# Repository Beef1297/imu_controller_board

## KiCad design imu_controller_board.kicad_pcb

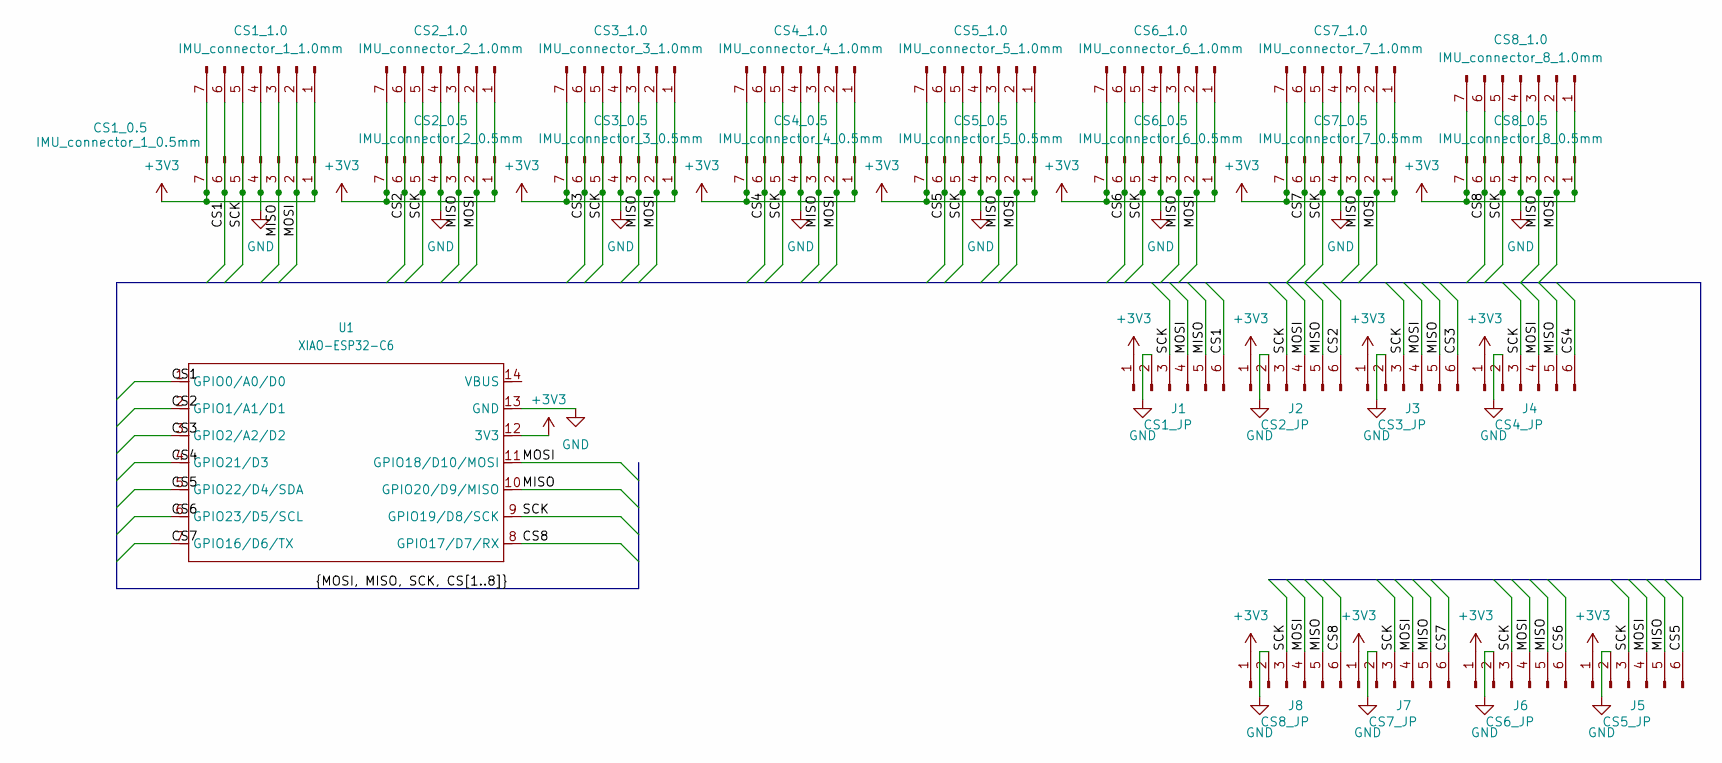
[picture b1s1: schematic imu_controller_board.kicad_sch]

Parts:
CS1_0.5: IMU_connector_1_0.5mm; FC-5A7P11H20-05pitch_7pin
CS1_1.0: IMU_connector_1_1.0mm; FPC-SMD_XUNPU_FPC-1.0FX-7PWCR-H20
CS2_0.5: IMU_connector_2_0.5mm; FC-5A7P11H20-05pitch_7pin
CS2_1.0: IMU_connector_2_1.0mm; FPC-SMD_XUNPU_FPC-1.0FX-7PWCR-H20
CS3_0.5: IMU_connector_3_0.5mm; FC-5A7P11H20-05pitch_7pin
CS3_1.0: IMU_connector_3_1.0mm; FPC-SMD_XUNPU_FPC-1.0FX-7PWCR-H20
CS4_0.5: IMU_connector_4_0.5mm; FC-5A7P11H20-05pitch_7pin
CS4_1.0: IMU_connector_4_1.0mm; FPC-SMD_XUNPU_FPC-1.0FX-7PWCR-H20
CS5_0.5: IMU_connector_5_0.5mm; FC-5A7P11H20-05pitch_7pin
CS5_1.0: IMU_connector_5_1.0mm; FPC-SMD_XUNPU_FPC-1.0FX-7PWCR-H20
CS6_0.5: IMU_connector_6_0.5mm; FC-5A7P11H20-05pitch_7pin
CS6_1.0: IMU_connector_6_1.0mm; FPC-SMD_XUNPU_FPC-1.0FX-7PWCR-H20
CS7_0.5: IMU_connector_7_0.5mm; FC-5A7P11H20-05pitch_7pin
CS7_1.0: IMU_connector_7_1.0mm; FPC-SMD_XUNPU_FPC-1.0FX-7PWCR-H20
CS8_0.5: IMU_connector_8_0.5mm; FC-5A7P11H20-05pitch_7pin
CS8_1.0: IMU_connector_8_1.0mm; FPC-SMD_XUNPU_FPC-1.0FX-7PWCR-H20
J1: CS1_JP; PinHeader_1x06_P2.54mm_Vertical
J2: CS2_JP; PinHeader_1x06_P2.54mm_Vertical
J3: CS3_JP; PinHeader_1x06_P2.54mm_Vertical
J4: CS4_JP; PinHeader_1x06_P2.54mm_Vertical
J5: CS5_JP; PinHeader_1x06_P2.54mm_Vertical
J6: CS6_JP; PinHeader_1x06_P2.54mm_Vertical
J7: CS7_JP; PinHeader_1x06_P2.54mm_Vertical
J8: CS8_JP; PinHeader_1x06_P2.54mm_Vertical
U1: XIAO-ESP32-C6; XIAO-ESP32C6-DIP

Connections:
+3V3: CS1_0.5.1, CS1_0.5.7, CS1_1.0.1, CS1_1.0.7, CS2_0.5.1, CS2_0.5.7, CS2_1.0.1, CS2_1.0.7, CS3_0.5.1, CS3_0.5.7, CS3_1.0.1, CS3_1.0.7, CS4_0.5.1, CS4_0.5.7, CS4_1.0.1, CS4_1.0.7, CS5_0.5.1, CS5_0.5.7, CS5_1.0.1, CS5_1.0.7, CS6_0.5.1, CS6_0.5.7, CS6_1.0.1, CS6_1.0.7, CS7_0.5.1, CS7_0.5.7, CS7_1.0.1, CS7_1.0.7, CS8_0.5.1, CS8_0.5.7, CS8_1.0.1, CS8_1.0.7, J1.1, J2.1, J3.1, J4.1, J5.1, J6.1, J7.1, J8.1, U1.12 (3V3)
/CS1: CS1_0.5.6, CS1_1.0.6, J1.6, U1.1 (GPIO0/A0/D0)
/CS2: CS2_0.5.6, CS2_1.0.6, J2.6, U1.2 (GPIO1/A1/D1)
/CS3: CS3_0.5.6, CS3_1.0.6, J3.6, U1.3 (GPIO2/A2/D2)
/CS4: CS4_0.5.6, CS4_1.0.6, J4.6, U1.4 (GPIO21/D3)
/CS5: CS5_0.5.6, CS5_1.0.6, J5.6, U1.5 (GPIO22/D4/SDA)
/CS6: CS6_0.5.6, CS6_1.0.6, J6.6, U1.6 (GPIO23/D5/SCL)
/CS7: CS7_0.5.6, CS7_1.0.6, J7.6, U1.7 (GPIO16/D6/TX)
/CS8: CS8_0.5.6, CS8_1.0.6, J8.6, U1.8 (GPIO17/D7/RX)
/MISO: CS1_0.5.3, CS1_1.0.3, CS2_0.5.3, CS2_1.0.3, CS3_0.5.3, CS3_1.0.3, CS4_0.5.3, CS4_1.0.3, CS5_0.5.3, CS5_1.0.3, CS6_0.5.3, CS6_1.0.3, CS7_0.5.3, CS7_1.0.3, CS8_0.5.3, CS8_1.0.3, J1.5, J2.5, J3.5, J4.5, J5.5, J6.5, J7.5, J8.5, U1.10 (GPIO20/D9/MISO)
/MOSI: CS1_0.5.2, CS1_1.0.2, CS2_0.5.2, CS2_1.0.2, CS3_0.5.2, CS3_1.0.2, CS4_0.5.2, CS4_1.0.2, CS5_0.5.2, CS5_1.0.2, CS6_0.5.2, CS6_1.0.2, CS7_0.5.2, CS7_1.0.2, CS8_0.5.2, CS8_1.0.2, J1.4, J2.4, J3.4, J4.4, J5.4, J6.4, J7.4, J8.4, U1.11 (GPIO18/D10/MOSI)
/SCK: CS1_0.5.5, CS1_1.0.5, CS2_0.5.5, CS2_1.0.5, CS3_0.5.5, CS3_1.0.5, CS4_0.5.5, CS4_1.0.5, CS5_0.5.5, CS5_1.0.5, CS6_0.5.5, CS6_1.0.5, CS7_0.5.5, CS7_1.0.5, CS8_0.5.5, CS8_1.0.5, J1.3, J2.3, J3.3, J4.3, J5.3, J6.3, J7.3, J8.3, U1.9 (GPIO19/D8/SCK)
GND: CS1_0.5.4, CS1_1.0.4, CS2_0.5.4, CS2_1.0.4, CS3_0.5.4, CS3_1.0.4, CS4_0.5.4, CS4_1.0.4, CS5_0.5.4, CS5_1.0.4, CS6_0.5.4, CS6_1.0.4, CS7_0.5.4, CS7_1.0.4, CS8_0.5.4, CS8_1.0.4, J1.2, J2.2, J3.2, J4.2, J5.2, J6.2, J7.2, J8.2, U1.13 (GND)

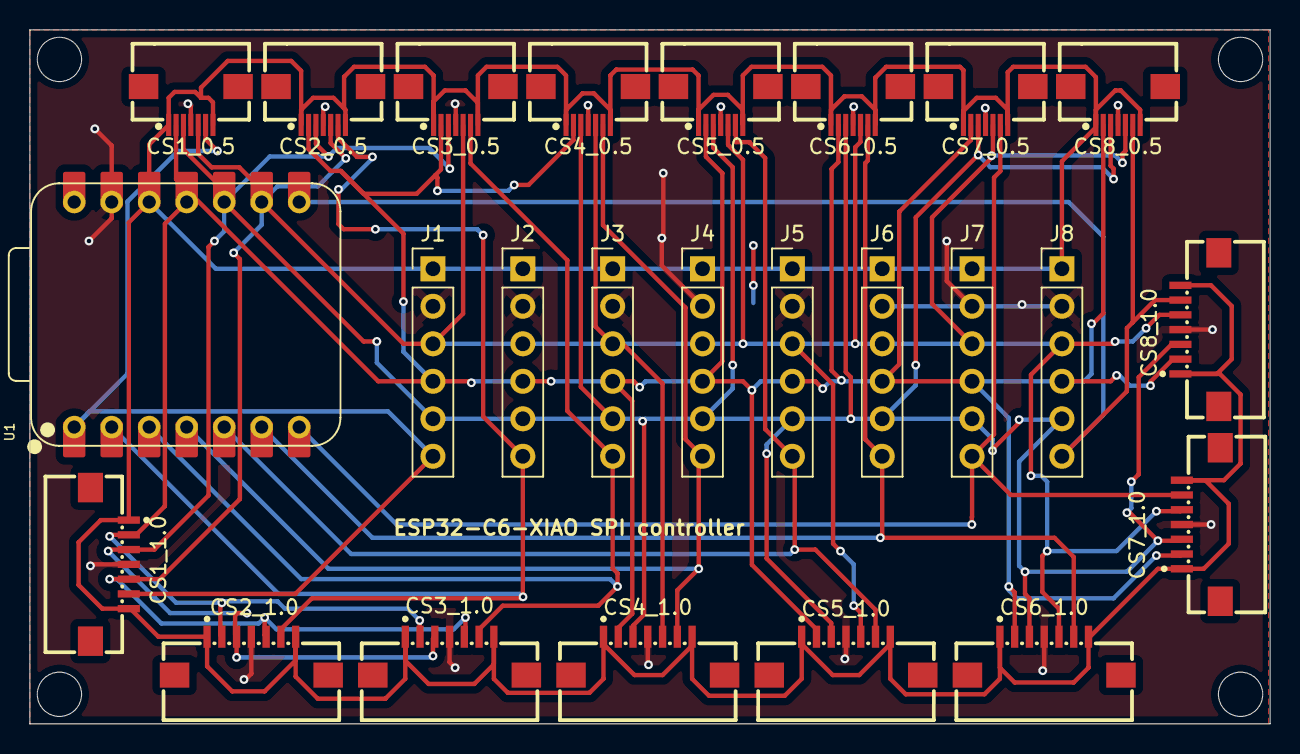
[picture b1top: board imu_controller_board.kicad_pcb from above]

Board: 2 copper layers, 84.0 x 47.0 mm, 25 parts (0 on the bottom side), 13 nets.

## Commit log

2025-08-22 v1 but mistake of directions
2025-08-25 let's create two versions
2025-08-25 added .gitignore
2025-08-25 created one-sided board and ordered it on JLCPCB
2025-08-25 added project file
